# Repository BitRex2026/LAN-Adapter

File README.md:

Lan Adapter 
------------------------------------------------------------------------------------------------------------------------
Suitable for any bitaxe and NerdQaxe variant miners that use T-Display S3 as the controller with esp-miner firmware
LAN Adapter supports :
NerdOctaxe Gamma
....
--------------------------------------------------------------------------------------------------
How to flash/update firmware
The newest releases are always here:
https://github.com/shufps/ESP-Miner-NerdQAxePlus/releases

Recommended Method: The Webflasher
---------------------------------------------------------------------------------------------------
The [Webflasher](https://shufps.github.io/nerdqaxe-web-flasher/) (modified fork of the great [Bitaxe Webflasher](https://github.com/bitaxeorg/bitaxe-web-flasher) by [Wantclue](https://github.com/WantClue)) is the easiest method of updating all Nerd*axe variants.

It uses the official releases published on this repository and is always up-to-date.

----------------------------------------------------------------------------------------------------
Donate: 

bc1qc6kzqynntf7y06t3e5d5lzzw3s4txmc5yhwlyk

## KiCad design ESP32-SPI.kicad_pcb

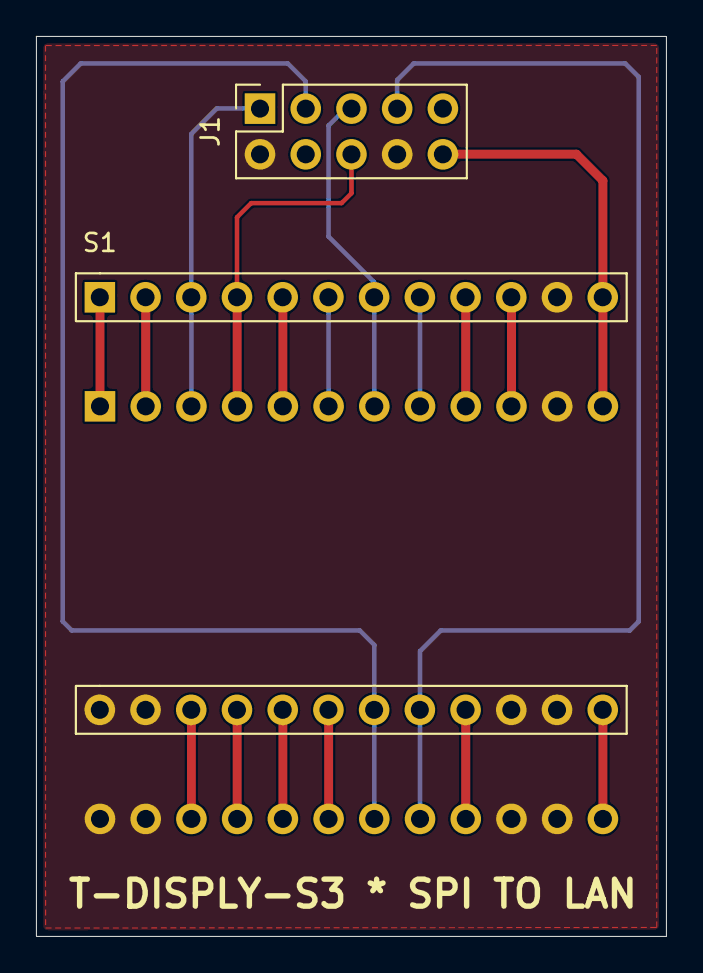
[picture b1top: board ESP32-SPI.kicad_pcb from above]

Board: 2 copper layers, 35.0 x 50.0 mm, 3 parts (1 on the bottom side), 20 nets.

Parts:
H1: PinHeader_T-DISPLAY-S3
J1: SPI-Connector; PinSocket_2x05_P2.54mm_Vertical
S1: PinSocket_T-DISPLAY-S3

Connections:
/1: H1.1 (3V), S1.1 (3V)
/2: H1.2 (GPIO1), S1.2 (GPIO1)
/3-SCLK: H1.3 (GPIO2), J1.1, S1.3 (GPIO2)
/4-RST: H1.4 (GPIO3), J1.6, S1.4 (GPIO3)
/5: H1.5 (GPIO10), S1.5 (GPIO10)
/5V: H1.12 (5V), J1.10, S1.12 (5V)
/6: H1.6 (GPIO11), S1.6 (GPIO11)
/7-MOSI: H1.7 (GPIO12), J1.5, S1.7 (GPIO12)
/8: H1.8 (GPIO13), S1.8 (GPIO13)
/9: H1.9 (NC), S1.9 (NC)
/10: H1.10 (NC), S1.10 (NC)
/13: H1.13 (3V), S1.13 (3V)
/16: H1.16 (NC), S1.16 (NC)
/17-MISO: H1.17 (GPIO16), J1.7, S1.17 (GPIO16)
/18-SCS: H1.18 (GPIO21), J1.3, S1.18 (GPIO21)
/19: H1.19 (GPIO17), S1.19 (GPIO17)
/20: H1.20 (GPIO18), S1.20 (GPIO18)
/21: H1.21 (GPIO44), S1.21 (GPIO44)
/22: H1.22 (GPIO43), S1.22 (GPIO43)
/GND: H1.11 (GND), H1.14 (GND), H1.15 (GND), H1.23 (GND), H1.24 (GND), J1.2, J1.8, S1.11 (GND), S1.14 (GND), S1.15 (GND), S1.23 (GND), S1.24 (GND)
